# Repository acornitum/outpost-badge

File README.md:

# Outpost badges!

These are e-ink badges that I made for Outpost! They're built with the RP2354 and have an onboard e-ink driver - I also did the art on it :D

Includes:
- 2.9in e-ink screen
- NFC capabilities
- 6 tactile buttons that snap right onto the board
- 15 additional gpio pins broken out to use with the perfboard at the bottom
- USB-C for power and programming
- 3 lanyard holes that fit single + double clip lanyards, and badge clips
- 4 mounting holes in case you want to 3d print a case 

[Here](https://user-cdn.hackclub-assets.com/019ff91c-0464-7b39-83fa-bce072a783c1/img_1220__yafw_balanced_.mp4) is a video of flappy bird on it! Firmware by [@SamDev-7](https://github.com/SamDev-7)

You can also use it to play doom (the badge is only used as a monitor + input in this gif) :D

---

### PCB + schematic:

---

HUGE thanks to [@cyao](https://github.com/cheyao) for helping with the design, and ordering the boards! The badge would not have worked without the countless reviews and feedback. 

Additional thanks to [@mpkendall](https://github.com/mpkendall) and [@KaiPereira](https://github.com/KaiPereira) for reviewing the board!

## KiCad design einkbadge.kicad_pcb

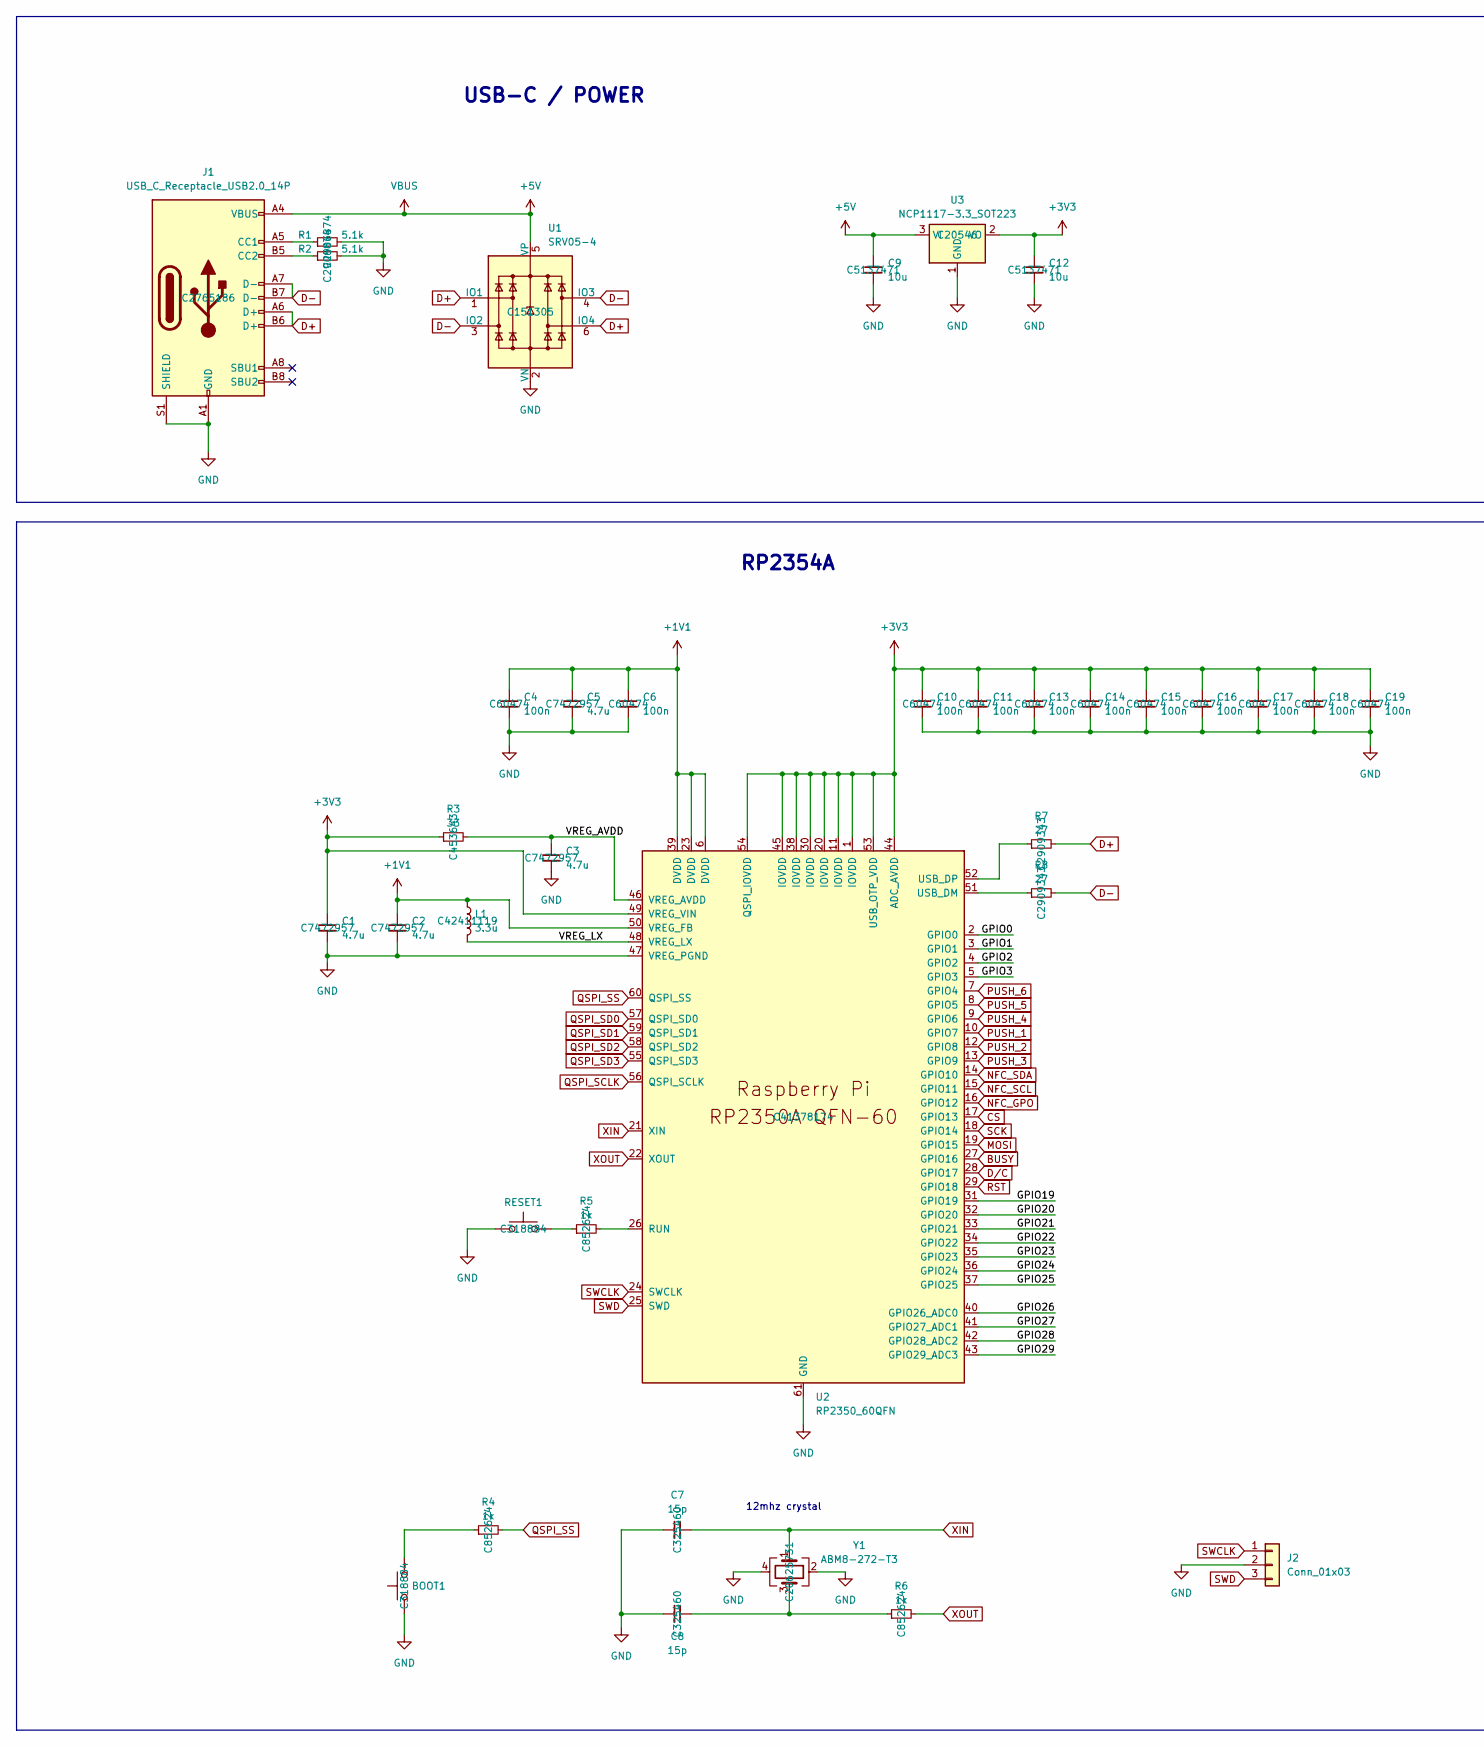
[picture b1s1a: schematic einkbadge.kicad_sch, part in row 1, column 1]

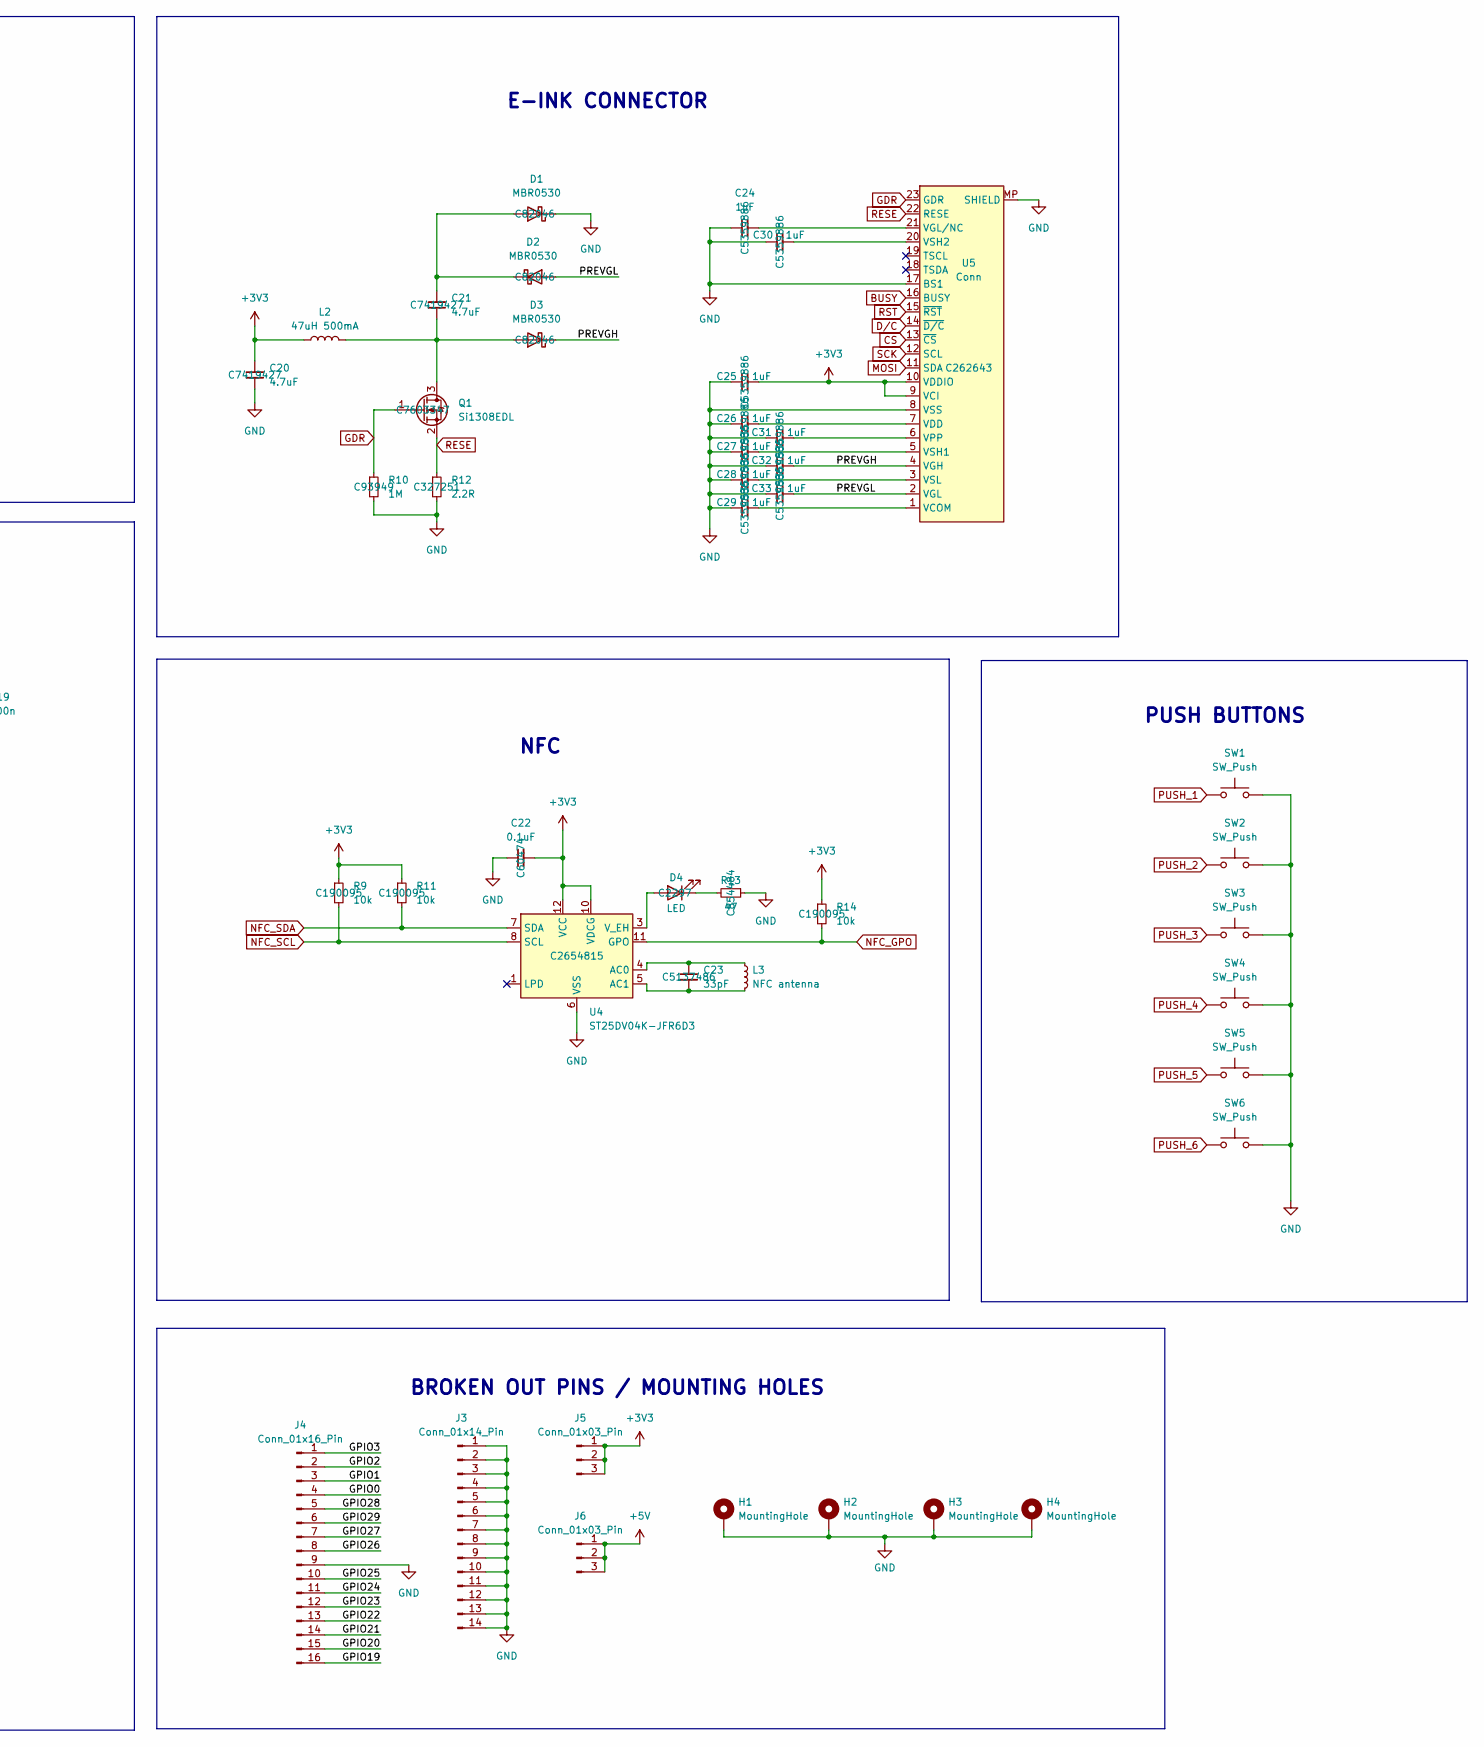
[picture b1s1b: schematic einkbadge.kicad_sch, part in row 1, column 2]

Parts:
BOOT1: BOOT; SW_Push_1P1T_XKB_TS-1187A; LCSC Part # C318884
C1, C2: 4.7u; Capacitor 0402; LCSC Part # C7472957
C3, C5: 4.7u; C_0402_1005Metric; LCSC Part # C7472957
C4, C6, C10, C11, C13, C14, C15, C16, C17, C18, C19: 100n; C_0402_1005Metric; LCSC Part # C60474
C7, C8: 15p; C_0402_1005Metric; LCSC Part # C325460
C9, C12: 10u; C_0805_2012Metric; LCSC Part # C5137471
C20, C21: 4.7uF; C_0603_1608Metric; LCSC Part # C7419427
C22: 0.1uF; C_0402_1005Metric; LCSC Part # C60474
C23: 33pF; C_0402_1005Metric; LCSC Part # C5137486
C24, C25, C26, C27, C28, C29, C30, C31, C32, C33: 1uF; C_0402_1005Metric; LCSC Part # C5359886
D1, D2, D3: MBR0530; D_SOD-123; LCSC Part # C82046
D4: LED; LED_0805_2012Metric; LCSC Part # C2297
H1, H2, H3, H4: MountingHole; MountingHole_2.2mm_M2_Pad_Via
J1: USB_C_Receptacle_USB2.0_14P; USB_C_Receptacle_GCT_USB4105-xx-A_16P_TopMnt_Horizontal; LCSC Part # C2765186
J2: Conn_01x03; PinHeader_1x03_P2.54mm_Vertical
J3: Conn_01x14_Pin; PinHeader_1x14_P2.54mm_Vertical
J4: Conn_01x16_Pin; PinHeader_1x16_P2.54mm_Vertical
J5, J6: Conn_01x03_Pin; PinHeader_1x03_P2.54mm_Vertical
L1: 3.3u; Abracon AOTA-B201610S3R3-101-T; LCSC Part # C42411119
L2: 47uH 500mA; L_APV_ANR4018; LCSC Part # C167808
L3: NFC antenna; KiCadAntenna
Q1: Si1308EDL; SOT-323_SC-70; LCSC Part # C7603347
R1, R2: 5.1k; R_0402_1005Metric; LCSC Part # C2906874
R3: 33; R_0402_1005Metric; LCSC Part # C453643
R4, R5, R6: 1k; R_0402_1005Metric; LCSC Part # C852624
R7, R8: 27; R_0402_1005Metric; LCSC Part # C2909343
R9, R11, R14: 10k; R_0402_1005Metric; LCSC Part # C190095
R10: 1M; R_0402_1005Metric; LCSC Part # C93949
R12: 2.2R; R_0402_1005Metric; LCSC Part # C327251
R13: 47; R_0402_1005Metric; LCSC Part # C854484
RESET1: RESET; SW_Push_1P1T_XKB_TS-1187A; LCSC Part # C318884
SW1, SW2, SW3, SW4, SW5, SW6: SW_Push; SW_PUSH-12mm_Wuerth-430476085716
U1: SRV05-4; SOT-23-6; LCSC Part # C151305
U2: RP2350_60QFN; QFN-60-1EP_7x7mm_P0.4mm_EP3.4x3.4mm_ThermalVias; LCSC Part # C41378174
U3: NCP1117-3.3_SOT223; SOT-223-3_TabPin2; LCSC Part # C20546
U4: ST25DV04K-JFR6D3; ST_UFDFPN-12-1EP_3x3mm_P0.5mm_EP1.4x2.55mm; LCSC Part # C2654815
U5: Conn; Jushuo_AFC07-S24FCA-00_1x24-1MP_P0.50_Horizontal; LCSC Part # C262643
Y1: ABM8-272-T3; Crystal_SMD_3225-4Pin_3.2x2.5mm; LCSC Part # C20625731

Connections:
+1V1: C2.1, C4.1, C5.1, C6.1, L1.1, U2.6 (DVDD), U2.23 (DVDD), U2.39 (DVDD), U2.50 (VREG_FB)
+3V3: C1.1, C10.1, C11.1, C12.1, C13.1, C14.1, C15.1, C16.1, C17.1, C18.1, C19.1, C20.1, C22.2, C25.2, J5.1, J5.2, J5.3, L2.1, R3.1, R9.1, R11.1, R14.1, U2.1 (IOVDD), U2.11 (IOVDD), U2.20 (IOVDD), U2.30 (IOVDD), U2.38 (IOVDD), U2.44 (ADC_AVDD), U2.45 (IOVDD), U2.49 (VREG_VIN), U2.53 (USB_OTP_VDD), U2.54 (QSPI_IOVDD), U3.2 (VO), U4.10 (VDCG), U4.12 (VCC), U5.9 (VCI), U5.10 (VDDIO)
+5V: C9.1, J1.A4 (VBUS), J1.A9 (VBUS), J1.B4 (VBUS), J1.B9 (VBUS), J6.1, J6.2, J6.3, U1.5 (VP), U3.3 (VI)
/GPIO0: J4.4, U2.2 (GPIO0)
/GPIO1: J4.3, U2.3 (GPIO1)
/GPIO2: J4.2, U2.4 (GPIO2)
/GPIO3: J4.1, U2.5 (GPIO3)
/GPIO19: J4.16, U2.31 (GPIO19)
/GPIO20: J4.15, U2.32 (GPIO20)
/GPIO21: J4.14, U2.33 (GPIO21)
/GPIO22: J4.13, U2.34 (GPIO22)
/GPIO23: J4.12, U2.35 (GPIO23)
/GPIO24: J4.11, U2.36 (GPIO24)
/GPIO25: J4.10, U2.37 (GPIO25)
/GPIO26: J4.8, U2.40 (GPIO26_ADC0)
/GPIO27: J4.7, U2.41 (GPIO27_ADC1)
/GPIO28: J4.5, U2.42 (GPIO28_ADC2)
/GPIO29: J4.6, U2.43 (GPIO29_ADC3)
/PREVGH: C32.2, D3.1 (K), U5.4 (VGH)
/PREVGL: C33.2, D2.2 (A), U5.2 (VGL)
/VREG_AVDD: C3.1, R3.2, U2.46 (VREG_AVDD)
/VREG_LX: L1.2, U2.48 (VREG_LX)
BUSY: U2.27 (GPIO16), U5.16 (BUSY)
CS: U2.17 (GPIO13), U5.13 (~CS)
D+: J1.A6 (D+), J1.B6 (D+), R7.2, U1.1 (IO1), U1.6 (IO4)
D-: J1.A7 (D-), J1.B7 (D-), R8.2, U1.3 (IO2), U1.4 (IO3)
D/C: U2.28 (GPIO17), U5.14 (~D/C)
GDR: Q1.1 (G), R10.1, U5.23 (GDR)
GND: BOOT1.1, C1.2, C2.2, C3.2, C4.2, C5.2, C6.2, C7.1, C8.1, C9.2, C10.2, C11.2, C12.2, C13.2, C14.2, C15.2, C16.2, C17.2, C18.2, C19.2, C20.2, C22.1, C24.1, C25.1, C26.1, C27.1, C28.1, C29.1, C30.1, C31.1, C32.1, C33.1, D1.1 (K), H1.1 (1_1), H2.1 (1_1), H3.1 (1_1), H4.1 (1_1), J1.A1 (GND), J1.A12 (GND), J1.B1 (GND), J1.B12 (GND), J1.S1 (SHIELD), J2.2, J3.1, J3.2, J3.3, J3.4, J3.5, J3.6, J3.7, J3.8, J3.9, J3.10, J3.11, J3.12, J3.13, J3.14, J4.9, R1.2, R2.2, R10.2, R12.2, R13.1, RESET1.1, SW1.2, SW2.2, SW3.2, SW4.2, SW5.2, SW6.2, U1.2 (VN), U2.47 (VREG_PGND), U2.61 (GND), U3.1 (GND), U4.6 (VSS), U5.8 (VSS), U5.17 (BS1), U5.MP (SHIELD), Y1.2, Y1.4
MOSI: U2.19 (GPIO15), U5.11 (SDA)
NFC_GPO: R14.2, U2.16 (GPIO12), U4.11 (GPO)
NFC_SCL: R9.2, U2.15 (GPIO11), U4.8 (SCL)
NFC_SDA: R11.2, U2.14 (GPIO10), U4.7 (SDA)
unnamed: BOOT1.2, R4.1
unnamed: C8.2, R6.1, Y1.3
unnamed: C21.2, D1.2 (A), D2.1 (K)
unnamed: C21.1, D3.2 (A), L2.2, Q1.3 (D)
unnamed: D4.2 (A), U4.3 (V_EH)
unnamed: D4.1 (K), R13.2
unnamed: J1.A5 (CC1), R1.1
unnamed: J1.B5 (CC2), R2.1
unnamed: R5.1, RESET1.2
unnamed: R5.2, U2.26 (RUN)
unnamed: R8.1, U2.51 (USB_DM)
unnamed: R7.1, U2.52 (USB_DP)
unnamed: C23.1, L3.1, U4.4 (AC0)
unnamed: C23.2, L3.2, U4.5 (AC1)
unnamed: C29.2, U5.1 (VCOM)
unnamed: C26.2, U5.7 (VDD)
unnamed: C24.2, U5.21 (VGL/NC)
unnamed: C31.2, U5.6 (VPP)
unnamed: C27.2, U5.5 (VSH1)
unnamed: C30.2, U5.20 (VSH2)
unnamed: C28.2, U5.3 (VSL)
PUSH_1: SW1.1, U2.10 (GPIO7)
PUSH_2: SW2.1, U2.12 (GPIO8)
PUSH_3: SW3.1, U2.13 (GPIO9)
PUSH_4: SW4.1, U2.9 (GPIO6)
PUSH_5: SW5.1, U2.8 (GPIO5)
PUSH_6: SW6.1, U2.7 (GPIO4)
QSPI_SCLK: U2.56 (QSPI_SCLK)
QSPI_SD0: U2.57 (QSPI_SD0)
QSPI_SD1: U2.59 (QSPI_SD1)
QSPI_SD2: U2.58 (QSPI_SD2)
QSPI_SD3: U2.55 (QSPI_SD3)
QSPI_SS: R4.2, U2.60 (QSPI_SS)
RESE: Q1.2 (S), R12.1, U5.22 (RESE)
RST: U2.29 (GPIO18), U5.15 (~RST)
SCK: U2.18 (GPIO14), U5.12 (SCL)
SWCLK: J2.1, U2.24 (SWCLK)
SWD: J2.3, U2.25 (SWD)
XIN: C7.2, U2.21 (XIN), Y1.1
XOUT: R6.2, U2.22 (XOUT)

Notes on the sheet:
USB-C / POWER
RP2354A
PUSH BUTTONS
NFC
12mhz crystal
E-INK CONNECTOR
BROKEN OUT PINS / MOUNTING HOLES

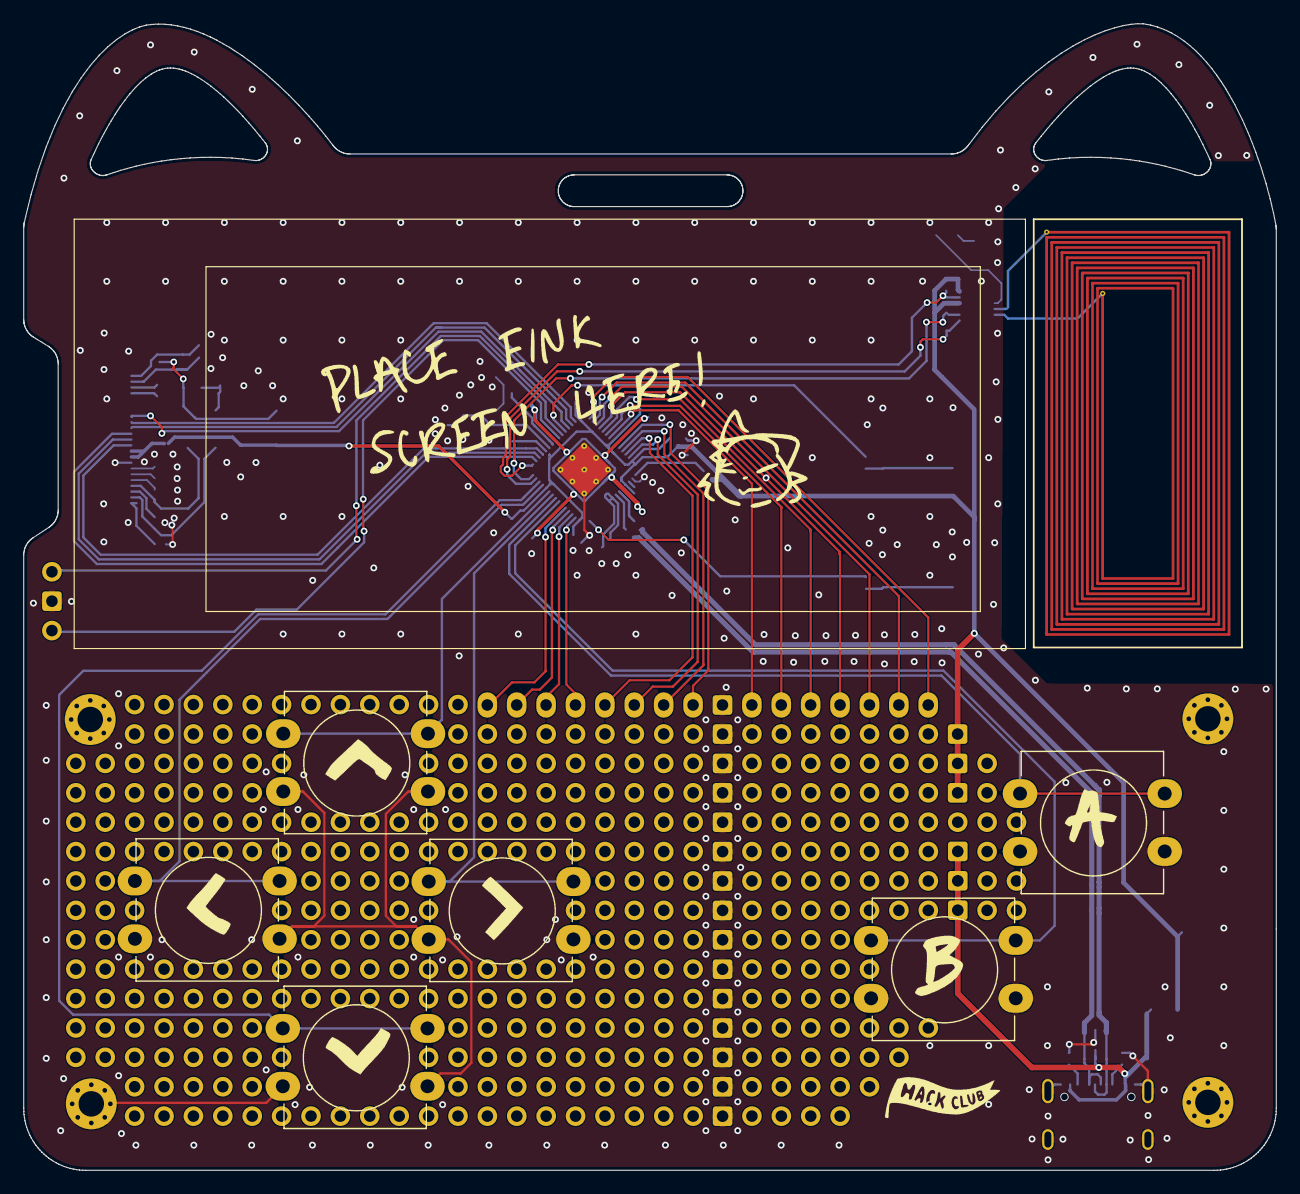
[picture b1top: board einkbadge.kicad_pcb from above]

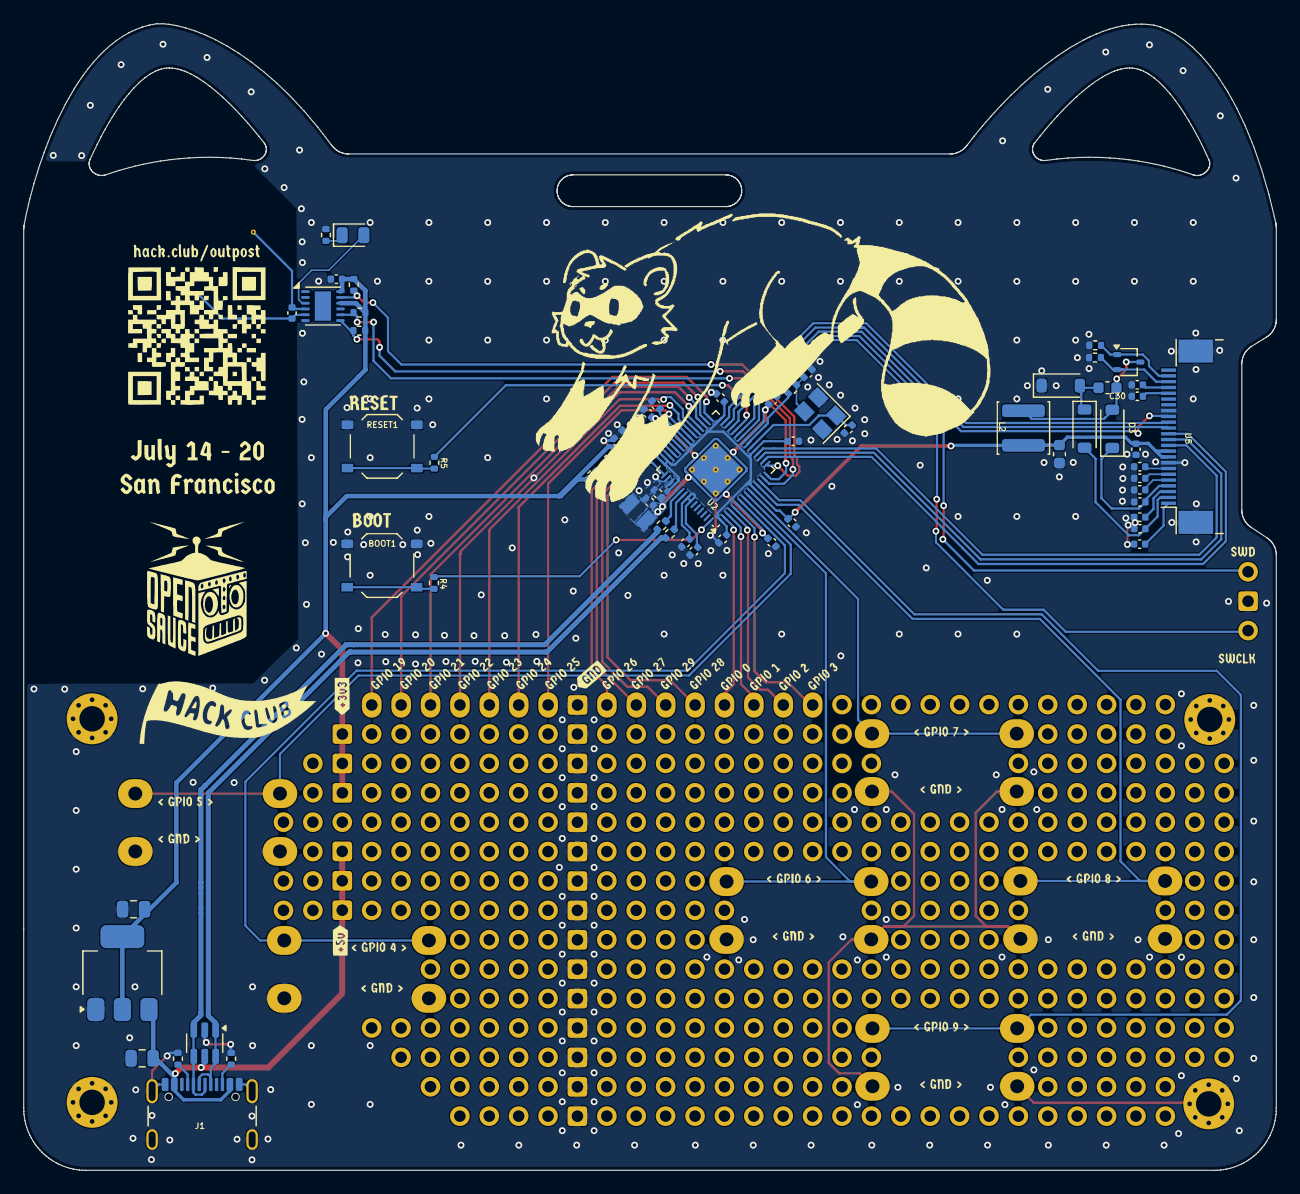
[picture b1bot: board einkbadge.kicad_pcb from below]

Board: 2 copper layers, 108.2 x 99.1 mm, 79 parts (64 on the bottom side), 68 nets.

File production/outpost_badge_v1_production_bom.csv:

Designator,Footprint,Quantity,Value,LCSC Part #
BOOT1,SW_Push_1P1T_XKB_TS-1187A,1,BOOT,
"C1, C2",Capacitor 0402,2,4.7u,
"C10, C11, C13, C14, C15, C16, C17, C18, C19, C4, C6",0402,11,100n,
"C12, C9",0805,2,10u,
"C20, C21",0603,2,4.7uF,
C22,0402,1,0.1uF,
C23,0402,1,33pF,
"C24, C25, C26, C27, C28, C29, C30, C31, C32, C33",0402,10,1uF,
"C3, C5",0402,2,4.7u,
"C7, C8",0402,2,15p,
"D1, D2, D3",D_SOD-123,3,MBR0530,
D4,0805,1,LED,
J1,USB_C_Receptacle_GCT_USB4105-xx-A_16P_TopMnt_Horizontal,1,USB_C_Receptacle_USB2.0_14P,
J2,PinHeader_1x03_P2.54mm_Vertical,1,Conn_01x03,
J3,PinHeader_1x14_P2.54mm_Vertical,1,Conn_01x14_Pin,
J4,PinHeader_1x16_P2.54mm_Vertical,1,Conn_01x16_Pin,
"J5, J6",PinHeader_1x03_P2.54mm_Vertical,2,Conn_01x03_Pin,
L1,Abracon AOTA-B201610S3R3-101-T,1,3.3u,
L2,L_APV_ANR4018,1,47uH 500mA,C167808
L3,KiCadAntenna,1,NFC antenna,
Q1,SOT-323_SC-70,1,Si1308EDL,
"R1, R2",0402,2,5.1k,
R10,0402,1,1M,
"R11, R14, R9",0402,3,10k,
R12,0402,1,2.2R,
R13,0402,1,47,
R3,0402,1,33,
"R4, R5, R6",0402,3,1k,
"R7, R8",0402,2,27,
RESET1,SW_Push_1P1T_XKB_TS-1187A,1,RESET,
"SW1, SW2, SW3, SW4, SW5, SW6",SW_PUSH-12mm_Wuerth-430476085716,6,SW_Push,
U1,SOT-23-6,1,SRV05-4,
U2,QFN-60-1EP_7x7mm_P0.4mm_EP3.4x3.4mm_ThermalVias,1,RP2350_60QFN,
U3,SOT-223-3_TabPin2,1,NCP1117-3.3_SOT223,
U4,ST_UFDFPN-12-1EP_3x3mm_P0.5mm_EP1.4x2.55mm,1,ST25DV04K-JFR6D3,
U5,Jushuo_AFC07-S24FCA-00_1x24-1MP_P0.50_Horizontal,1,Conn,C262567
Y1,Crystal_SMD_3225-4Pin_3.2x2.5mm,1,ABM8-272-T3,

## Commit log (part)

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2026-06-17 update schematic
2026-06-22 pcb routing almost done
2026-06-22 update pcb
2026-06-22 fix pcb
2026-06-23 pcb update (add gpio breakouts)
2026-06-26 add silkscreen, reroute eink connector
    also removed part label silkscreen
2026-06-26 added lcsc part numbers
2026-06-26 add production files
2026-06-26 update 1uf lcsc part
2026-06-28 minor routing fix
2026-06-29 Update silkscreen, soldermask and MPNs
2026-06-29 Fix bad git merge
